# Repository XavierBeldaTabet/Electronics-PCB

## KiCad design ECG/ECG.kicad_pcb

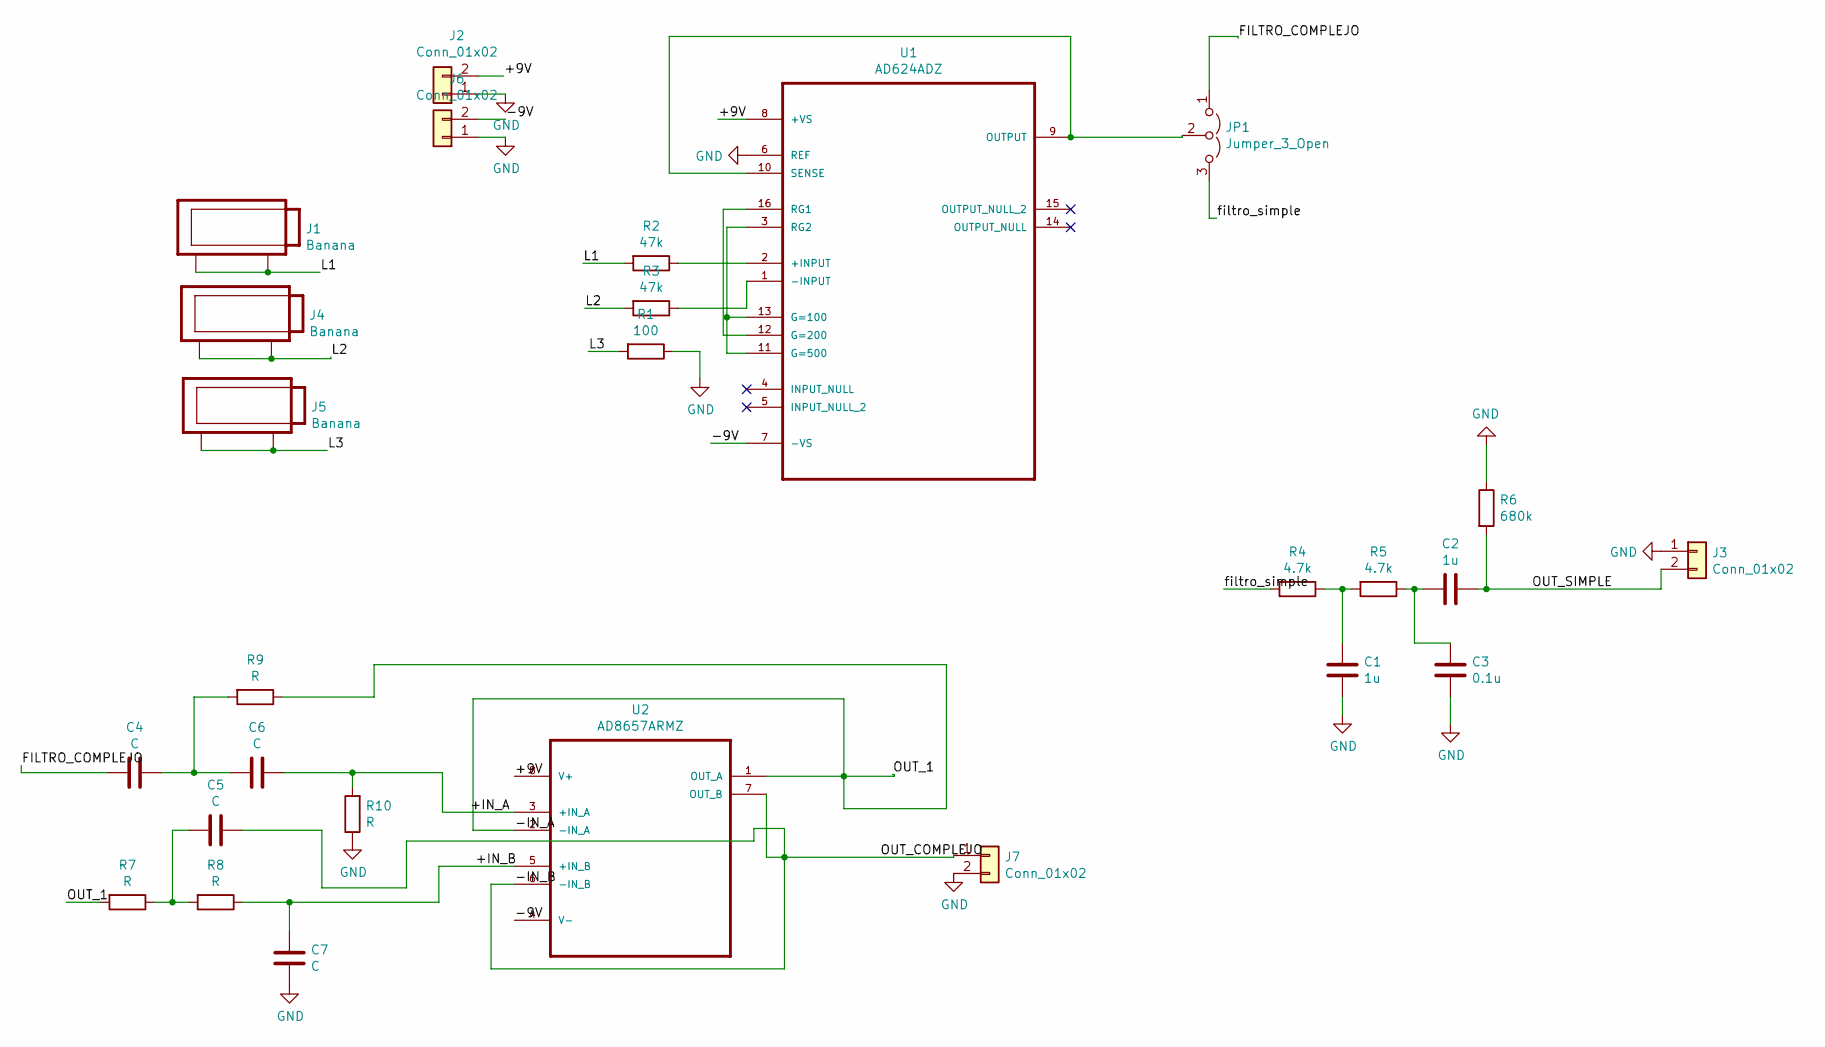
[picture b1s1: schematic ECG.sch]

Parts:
C1, C2: 1u; C_Radial_D4.0mm_H5.0mm_P1.50mm
C3: 0.1u; C_Radial_D4.0mm_H5.0mm_P1.50mm
C4, C5, C6, C7: C; C_Radial_D4.0mm_H5.0mm_P1.50mm
J1, J4, J5: Banana
J2, J3, J6, J7: Conn_01x02; PinHeader_1x02_P2.00mm_Vertical
JP1: Jumper_3_Open; PinHeader_1x03_P2.00mm_Vertical
R1: 100; R_Axial_DIN0207_L6.3mm_D2.5mm_P7.62mm_Horizontal
R2, R3: 47k; R_Axial_DIN0207_L6.3mm_D2.5mm_P7.62mm_Horizontal
R4, R5: 4.7k; R_Axial_DIN0207_L6.3mm_D2.5mm_P7.62mm_Horizontal
R6: 680k; R_Axial_DIN0207_L6.3mm_D2.5mm_P7.62mm_Horizontal
R7, R8, R9, R10: R; R_Axial_DIN0207_L6.3mm_D2.5mm_P7.62mm_Horizontal
U1: AD624ADZ; AD624
U2: AD8657ARMZ; SOP65P490X110-8N

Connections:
/+9V: J2.2, U1.8 (+VS), U2.8 (V+)
/+IN_A: C6.1, R10.2, U2.3 (+IN_A)
/+IN_B: C7.1, R8.1, U2.5 (+IN_B)
/-9V: J6.2, U1.7 (-VS), U2.4 (V-)
/-IN_A: R7.2, R9.1, U2.1 (OUT_A), U2.2 (-IN_A)
/-IN_B: C5.2, J7.1, U2.6 (-IN_B), U2.7 (OUT_B)
/FILTRO_COMPLEJO: C4.2, JP1.1 (A)
/L1: J1.1, J1.2, R2.2
/L2: J4.1, J4.2, R3.2
/L3: J5.1, J5.2, R1.2
/OUT_SIMPLE: C2.1, J3.2, R6.2
/filtro_simple: JP1.3 (B), R4.2
GND: C1.2, C3.2, C7.2, J2.1, J3.1, J6.1, J7.2, R1.1, R6.1, R10.1, U1.6 (REF)
unnamed: C1.1, R4.1, R5.2
unnamed: C2.2, C3.1, R5.1
unnamed: C4.1, C6.2, R9.2
unnamed: C5.1, R7.1, R8.2
unnamed: JP1.2 (C), U1.9 (OUTPUT), U1.10 (SENSE)
unnamed: R2.1, U1.2 (+INPUT)
unnamed: R3.1, U1.1 (-INPUT)
unnamed: U1.3 (RG2), U1.11 (G=500), U1.13 (G=100)
unnamed: U1.12 (G=200), U1.16 (RG1)

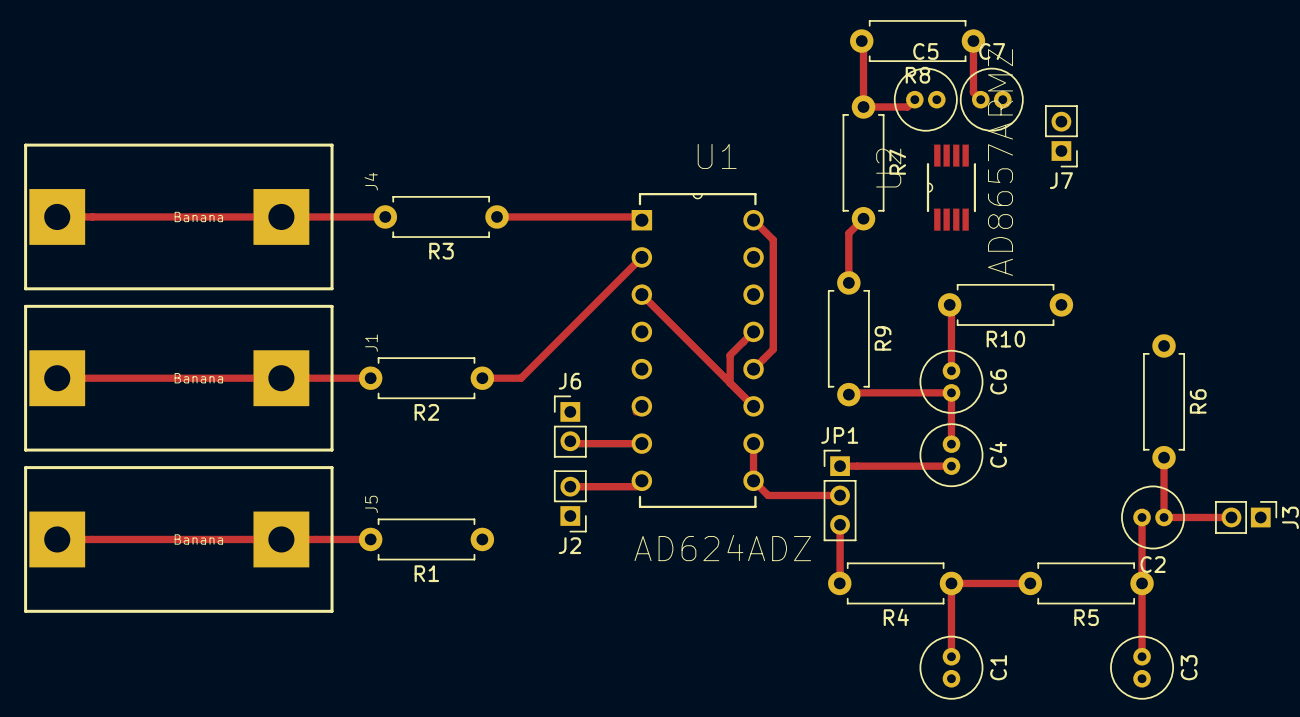
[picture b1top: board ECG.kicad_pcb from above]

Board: 2 copper layers, 27 parts (0 on the bottom side), 22 nets.

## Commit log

2019-03-13 Organising Repository
2019-03-14 added GPIO and SWD/JTAG connector
2019-03-15 footprint assignment to components
2019-03-21 footprint changes
